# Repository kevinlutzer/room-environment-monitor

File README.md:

# Overview 

The Room Environment Monitor (REM) project was something that I started back in 2017. I wanted a small IoT device that could tell me if there was a concerning amount of volatile organic compounds (VOCs) and CO2 in my workshop. I built the first version based on a Raspberry Pi Zero, CCS811 air quality monitor, and a BME280 humidity and temperature sensor.

I went through multiple iterations of the project with the overall objective to reduce cost while increasing the precision of the measurements being made. At that time, the CCS811 sensor cost about 40 dollars alone, which brought the V1 bill of materials (BOM) cost to about 70 CAD. Fast forward to 2023, Ikea released their [Vindriktning](https://www.ikea.com/ca/en/p/vindriktning-air-quality-sensor-60515911/) air quality monitor which uses a [PM1006K](https://en.gassensor.com.cn/Product_files/Specifications/LED%20Particle%20Sensor%20PM1006K%20Specification.pdf) sensor to measure 2.5um matter in the air. I designed my latest version of the Room Environment Monitor to replace the controller inside and make use of the device's case.

# Data Collection

The REM collects data from the following sensors:
1. [BME280](https://www.bosch-sensortec.com/products/environmental-sensors/humidity-sensors-bme280/) - Temperature, Humidity, Pressure
1. [SGP40-2.5k](https://sensirion.com/products/catalog/SGP40) - VOCs, C02  
1. [PM1006K](https://en.gassensor.com.cn/ParticulateMatterSensor/info_itemid_105.html) - particulate matter in the air (2.5ug/m^3, 1.0ug/m^3, 10ug/m^3)

This data is then pushed to a MQTT broker via the MQTT networking protocal. The broker then broadcasts the data to any subscribers. I use [n8n](https://n8n.io/) which is a workflow automation tool to subscribe to the REM data stream. n8n ensures that each piece of data in this stream is inserted as a new row in to a Postgres database. Bellow is a sequence diagram that shows how the data flows and is collected. 

<!-- https://sequencediagram.org/
title Room Environment Monitor Data Collection 

REM->MQTT Broker:publish data over tcp/ip using MQTT
MQTT Broker->n8n:broad cast data over tcp/ip using MQTT 
n8n->Postgres: insert new row  -->

<!-- # Data Visualization -->

I use Grafana, a free an open source tool to visualize the collected data in my Postgres database. Here is a screenshot of the dashboard that I have created to visualize the data.

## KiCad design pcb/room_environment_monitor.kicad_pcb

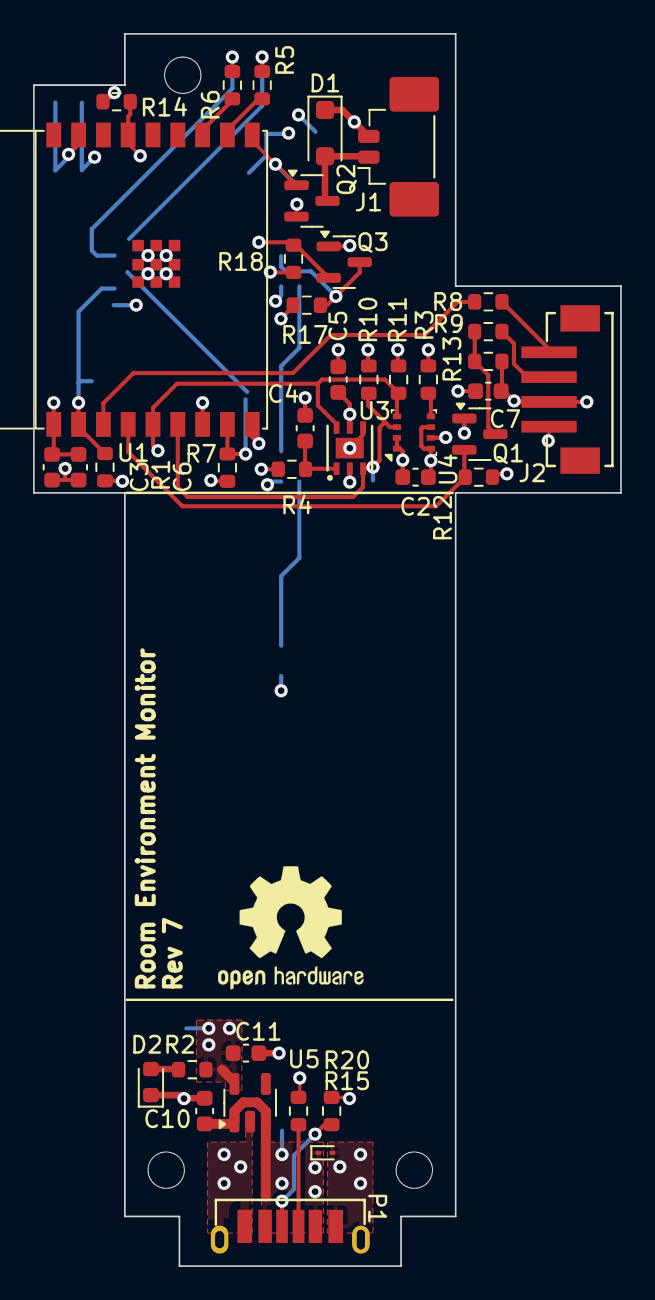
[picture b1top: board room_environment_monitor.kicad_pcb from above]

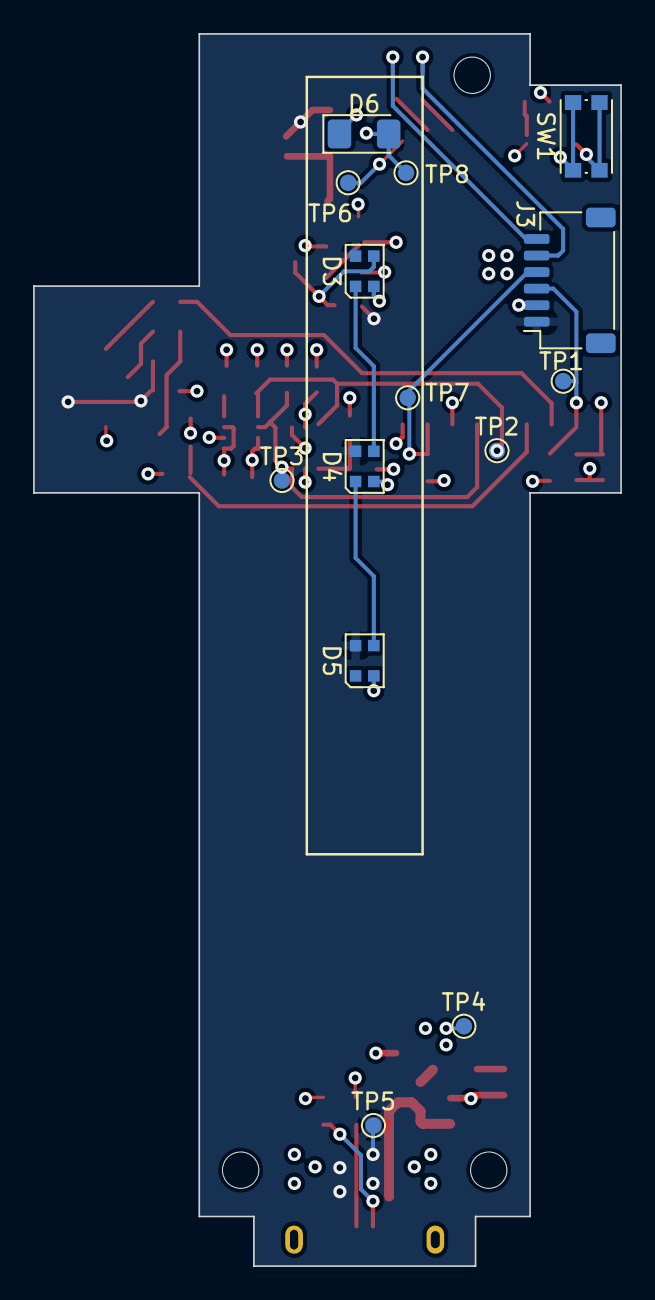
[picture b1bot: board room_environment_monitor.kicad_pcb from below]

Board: 4 copper layers, 35.5 x 74.5 mm, 56 parts (14 on the bottom side), 29 nets.

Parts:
C2, C3, C4, C5: 0u1; C_0603_1608Metric
C6, C7, C10, C11: 1u; C_0603_1608Metric
D1: CDBMS160; D_SOD-123F
D2: LED; LED_0603_1608Metric
D3, D4, D5: WS2812B-2020; LED_WS2812B-2020_PLCC4_2.0x2.0mm
D6: D_Photo; D_1206_3216Metric_Pad1.42x1.75mm_HandSolder
D7: ESD9X3; D_SOD-923
H1, H2, H3: MountingHole; MountingHole_2.2mm_M2_DIN965
J1: Conn_01x02_Pin; Molex_PicoBlade_53398-0271_1x02-1MP_P1.25mm_Vertical
J2: Conn_01x04_Pin; CONN_B4B-ZR-SM4-TF_JST
J3: Conn_01x06_Socket; JST_SH_SM06B-SRSS-TB_1x06-1MP_P1.00mm_Horizontal
P1: USB_C_Plug_USB2.0; CONN6_USB4130-GF-C_GCT
Q1, Q2, Q3: BSS138; SOT-23
R1, R3, R7, R12, R13, R17, R18: 10k; R_0603_1608Metric
R2: 220; R_0603_1608Metric
R4: 4.7; R_0603_1608Metric
R5, R6, R8, R9: 0; R_0603_1608Metric
R10, R11: 2k2; R_0603_1608Metric
R14: 10M; R_0603_1608Metric
R15, R20: 5.1k; R_0603_1608Metric
SW1: SW_SPST; SW_Push_1P1T_NO_CK_KMR2
TP1, TP2, TP3, TP4, TP5, TP6, TP7, TP8: TestPoint; TestPoint_Pad_D1.0mm
U1: ESP32-C3-WROOM-02
U3: SGP40; SGP30-2.5K_SEN-M
U4: BME280; Bosch_LGA-8_2.5x2.5mm_P0.65mm_ClockwisePinNumbering
U5: AP2112K-3.3; SOT-23-5

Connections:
+3V3: C2.1, C3.1, C5.1, C6.1, C11.1, D6.1 (K), Q1.1 (G), Q3.1 (G), R1.1, R2.1, R3.1, R4.1, R7.1, R10.2, R11.2, R12.1, R18.1, TP4.1, U1.1 (3V3), U3.5 (VDDH), U4.6 (VDDIO), U4.8 (VDD), U5.5 (VOUT)
+5V: C7.1, C10.1, D1.1 (K), D3.4 (VDD), D4.4 (VDD), D5.4 (VDD), D7.1 (K), J1.2, J2.3, J3.1, P1.A9 (VBUS), P1.B9 (VBUS), R13.1, R17.1, TP5.1, U5.1 (VIN), U5.3 (EN)
/NEOPIXEL_LVL: D3.3 (DIN), Q3.3 (D), R17.2
/Sensors/SGP30_VDD: C4.1, R4.2, U3.1 (VDD)
BOOT: J3.4, R7.2, TP7.1, U1.8 (GPIO9)
EN: J3.3, R1.2, TP1.1, U1.2 (EN/CHIP_PU)
FACT_REST: SW1.2 (B), U1.17 (GPIO1/ADC1_CH1/XTAL_32K_N)
FAN: Q2.1 (G), TP6.1, U1.10 (GPIO10)
GND: C2.2, C3.2, C4.2, C5.2, C6.2, C7.2, C10.2, C11.2, D2.1 (K), D3.2 (VSS), D4.2 (VSS), D5.2 (VSS), D7.2 (A), J2.4, J3.2, P1.A12 (GND), P1.B12 (GND), P1.S1 (SHIELD), Q2.2 (S), R14.1, R15.2, R20.2, SW1.1 (A), U1.9 (GND), U1.19 (GND), U3.2 (VSS), U3.4 (N/A), U3.7 (PAD), U4.1 (GND), U4.2 (CSB), U4.7 (GND), U5.2 (GND)
I2C_SCL: R11.1, TP2.1, U1.5 (GPIO6), U3.6 (SCL), U4.4 (SCK)
I2C_SDA: R10.1, TP3.1, U1.6 (GPIO7), U3.3 (SDA), U4.3 (SDI)
NEOPIXEL: Q3.2 (S), R18.2, U1.7 (GPIO8)
unnamed: D1.2 (A), J1.1, Q2.3 (D)
unnamed: D2.2 (A), R2.2
unnamed: D3.1 (DOUT), D4.3 (DIN)
unnamed: D4.1 (DOUT), D5.3 (DIN)
unnamed: J2.1, R8.1
unnamed: J2.2, R9.1
unnamed: J3.5, R6.2
unnamed: J3.6, R5.2
unnamed: P1.A5 (CC), R20.1
unnamed: P1.B5 (VCONN), R15.1
unnamed: R3.2, U4.5 (SDO)
PD: D6.2 (A), R14.2, TP8.1, U1.15 (GPIO3/ADC1_CH3)
UART1_RX: R8.2, U1.3 (GPIO4/ADC1_CH4)
UART1_TX: Q1.3 (D), R9.2, R13.2
UART1_TX_LVL: Q1.2 (S), R12.2, U1.4 (GPIO5/ADC2_CH0)
UART_RX: R6.1, U1.12 (GPIO21/U0TXD)
UART_TX: R5.1, U1.11 (GPIO20/U0RXD)

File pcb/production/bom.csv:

Designator,Footprint,Quantity,Value,LCSC Part #
"C1, C2, C3, C4, C5, C8",0603,6,0u1,
"C10, C11, C6, C7",0603,4,1u,
D1,D_SOD-123F,1,CDBMS160,
D2,0603,1,LED,
J1,Molex_PicoBlade_53398-0271_1x02-1MP_P1.25mm_Vertical,1,Conn_01x02_Pin,
J2,CONN_B4B-ZR-SM4-TF_JST,1,Conn_01x04_Pin,
"Q1, Q2",SOT-23,2,BSS138,
"R1, R12, R13, R16, R3, R7",0603,6,10k,
"R10, R11",0603,2,2k2,
"R15, R20",0603,2,5.1k,
R2,0603,1,220,
R4,0603,1,4.7,
"R5, R6, R8, R9",0603,4,0,
SW1,SW_Push_1P1T_NO_CK_KMR2,1,SW_SPST,
U1,DFN-8-1EP_3x2mm_P0.5mm_EP1.3x1.5mm,1,ATECC608A-MAHDA,
U2,ESP32-C3-MINI-1,1,ESP32-C3-MINI-1,
U3,SGP30-2.5K_SEN-M,1,SGP40,
U4,Bosch_LGA-8_2.5x2.5mm_P0.65mm_ClockwisePinNumbering,1,BME280,
U5,SOT-23-5,1,AP2112K-3.3,

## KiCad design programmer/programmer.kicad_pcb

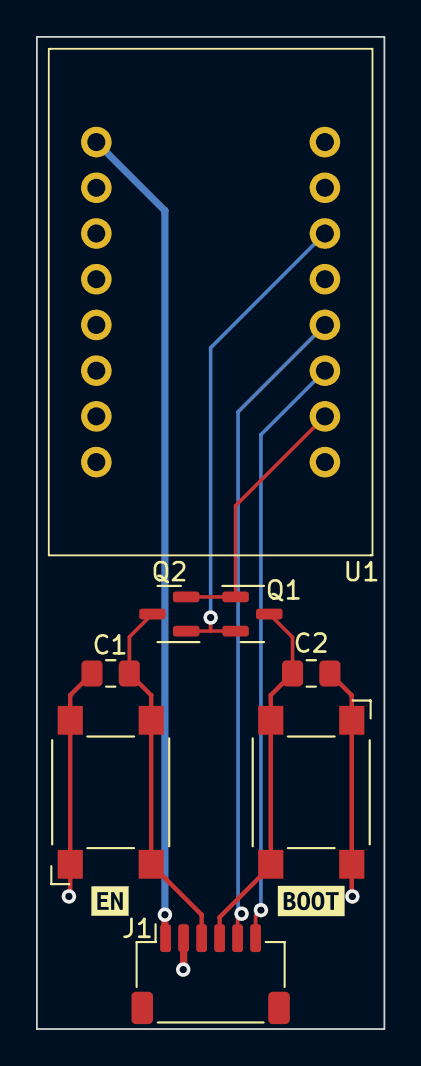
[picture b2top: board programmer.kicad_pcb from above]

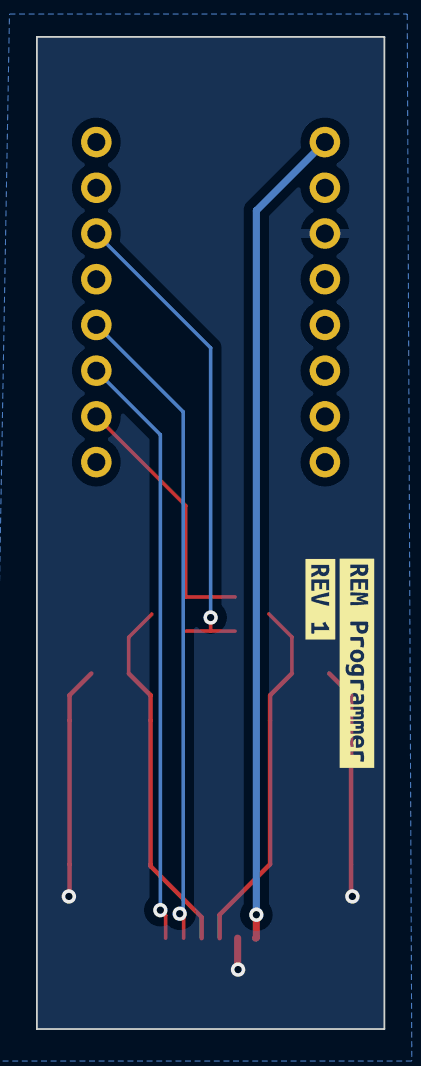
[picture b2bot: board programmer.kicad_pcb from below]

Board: 2 copper layers, 19.3 x 55.1 mm, 12 parts (2 on the bottom side), 8 nets.

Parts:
C1, C2: C; C_0805_2012Metric_Pad1.18x1.45mm_HandSolder
J1: Conn_01x06_Socket; JST_SH_SM06B-SRSS-TB_1x06-1MP_P1.00mm_Horizontal
Q1, Q2: BSS138; SOT-23
SW1, SW3: SW_Omron_B3FS; SW_SPST_Omron_B3FS-100xP
U1: Adafruit CP210XN Friend; Adafruit_CP210XN_Friend
kibuzzard-654D0F9E: G***; kibuzzard-654D0F9E
kibuzzard-654D0FC0: G***; kibuzzard-654D0FC0
kibuzzard-654D0FE8: G***; kibuzzard-654D0FE8
kibuzzard-654D1020: G***; kibuzzard-654D1020

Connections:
+5V: J1.1, U1.1 (VBUS)
BOOT: C2.1, J1.4, Q1.3 (D), SW3.2
DTR: Q1.2 (S), Q2.1 (G), U1.14 (DTR)
EN: C1.1, J1.3, Q2.3 (D), SW1.2
GND: C1.2, C2.2, J1.2, SW1.1, SW3.1, U1.3 (GND)
RTS: Q1.1 (G), Q2.2 (S), U1.10 (RTS)
UART_RX: J1.5, U1.12 (TXD)
UART_TX: J1.6, U1.11 (RXD)

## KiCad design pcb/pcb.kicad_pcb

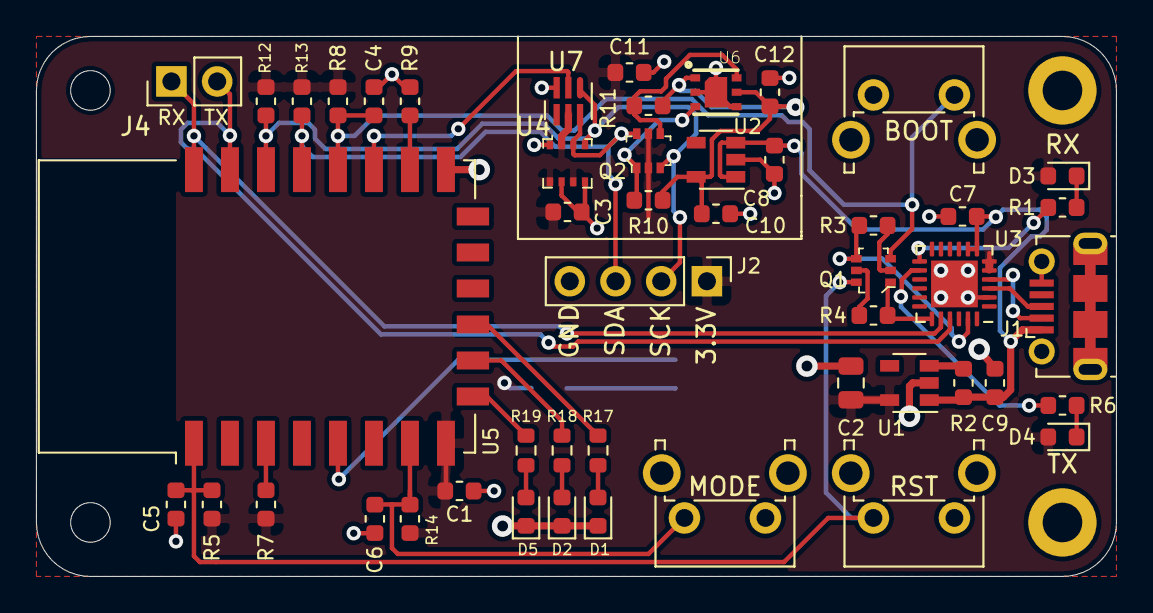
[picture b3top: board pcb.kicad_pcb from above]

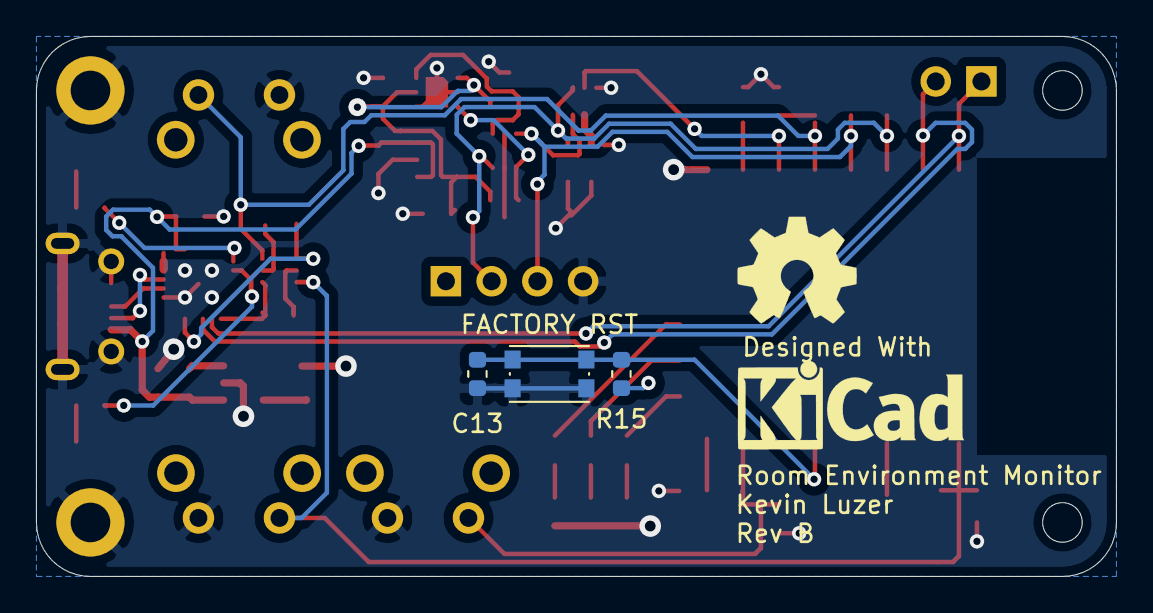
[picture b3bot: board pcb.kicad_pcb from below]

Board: 2 copper layers, 60.0 x 30.0 mm, 56 parts (3 on the bottom side), 34 nets.

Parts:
C1, C3, C4, C5, C6, C11, C12, C13: 100n; C_0603_1608Metric
C2: 47u; C_0805_2012Metric
C7, C8, C9, C10: 10u; C_0603_1608Metric
D1, D2, D3, D4, D5: LED; LED_0603_1608Metric
H1, H4: MountingHole_Pad; MountingHole_2.2mm_M2
H2, H3: MountingHole_Pad; MountingHole_2.2mm_M2_ISO14580_Pad
J1: USB_B_Mini; USB_Micro-B_Molex-105017-0001
J2: I2C_BUS; PinHeader_1x04_P2.54mm_Vertical
J4: UART_BUS; PinHeader_1x02_P2.54mm_Vertical
Q1, Q2: BSS138DW-7-F; SOT-363
R1, R6, R17, R18, R19: 470; R_0603_1608Metric
R2, R3, R4, R5, R7, R8, R9, R10, R11, R12, R13, R14, R15: 10k; R_0603_1608Metric
SW1, SW2, SW3: PTS645Vx83; SW_Tactile_SPST_Angled_PTS645Vx58-2LFS
SW4: KMR2; SW_Push_1P1T_NO_CK_KMR2
U1: AP2112K-3.3; SOT-23-5
U2: MIC5225-1.8YM5; SOT-23-5
U3: CP2104; QFN-24-1EP_4x4mm_P0.5mm_EP2.6x2.6mm
U4: BME280; Pressure_Sensor_LGA-8_2.5x2.5mm_BME280
U5: ESP-12F; ESP-12E
U6: SGP30
U7: TSL2591

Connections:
+1V8: C10.1, C12.1, R10.1, R11.1, U2.5, U6.1, U6.5
+3V3: C1.1, C2.1, C3.1, C11.1, D3.2, D4.2, J2.1, Q2.2, Q2.5, R5.1, R7.1, R8.1, R12.1, R13.1, R14.1, R15.1, U1.5, U3.5, U3.6, U4.2, U4.6, U4.8, U5.8, U7.5
+5V: C7.1, C8.1, C9.1, J1.1, R2.1, U1.1, U2.1, U2.3, U3.7, U3.8
GND: C1.2, C2.2, C3.2, C4.2, C5.2, C6.2, C7.2, C8.2, C9.2, C10.2, C11.2, C12.2, C13.2, D1.1, D2.1, D5.1, H2.1, H3.1, J1.5, J1.6, J2.4, R9.2, SW1.1, SW2.1, SW3.1, SW4.1, U1.2, U2.2, U3.2, U3.25, U4.1, U4.5, U4.7, U5.15, U6.2, U6.4, U6.7, U7.3
I2C_SCK: J2.2, Q2.3, R12.2, U4.4, U5.20, U7.1
I2C_SCK_1V8: Q2.4, R11.2, U6.6
I2C_SDA: J2.3, Q2.6, R13.2, U4.3, U5.19, U7.6
I2C_SDA_1V8: Q2.1, R10.2, U6.3
unnamed: D1.2, R17.1
unnamed: D2.2, R18.1
unnamed: D3.1, R1.1
unnamed: D4.1, R6.1
unnamed: D5.2, R19.1
unnamed: J1.2, U3.4
unnamed: J1.3, U3.3
unnamed: Q1.1, R4.2, U3.19
unnamed: Q1.2, R3.1
unnamed: Q1.4, R3.2, U3.23
unnamed: Q1.5, R4.1
unnamed: R1.2, U3.13
unnamed: R2.2, U1.3
unnamed: R6.2, U3.14
unnamed: R7.2, U5.3
unnamed: R9.1, U5.16
SIG1: R17.2, U5.11
SIG2: R18.2, U5.10
SIG3: R19.2, U5.9
UART_RX: J4.1, U3.20, U5.22
UART_TX: J4.2, U3.21, U5.21
nBOOT: C4.1, Q1.3, R8.2, SW2.2, U5.18
nFAC_RST: C13.1, R15.2, SW4.2, U5.5
nINT: U5.17, U7.2
nMODE: C6.1, R14.2, SW1.2, U5.7
nRST: C5.1, Q1.6, R5.2, SW3.2, U5.1

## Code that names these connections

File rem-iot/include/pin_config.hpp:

#ifndef _REM_PIN_CONFIG_HPP
#define _REM_PIN_CONFIG_HPP

#define PM1006K_RX_PIN 4
#define PM1006K_TX_PIN 5

#define FAN 10

#define I2C_SDA 7
#define I2C_SCL 6

#define NEOPIXEL_PIN 8
#define NUM_NEOPIXELS 3

#endif

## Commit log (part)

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2018-05-20 build iot functionality
2018-05-20 update service layer. Everything is working
2018-05-20 update main code for python to take in arguments to collect sensor data
2018-05-20 bring in dep
2018-05-20 fix import references
2018-05-20 remove uneeded commands
2018-05-20 file change
2018-05-20 WIP not sure why this isn't working --> Added io reader for std buffer
2018-05-21 WIP for concurrency
2018-05-21 Working version
2018-05-24 update service and sensor stuff
2018-05-24 add angular client
2018-05-26 make more progress on metric boxes
2018-05-26 add service and component
2018-05-26 refactor and make more progress flushing out the metric box
2018-05-29 add client files
2018-05-29 update logging
2018-05-29 get the server logs to make sense
2018-05-29 add python stub file
2018-05-29 update server logs
2018-09-12 update with cross platform compliation tool
2018-09-12 test signed
2018-09-13 add some base code I will need to in the entry point
2018-09-13 bring in gorobot
2018-09-13 refacor main.py to remove tsl stuff
2018-09-13 go fmt
2018-09-13 add binary file to gitignore list
2018-09-15 removed initaialize method until I can fix bugs in the gobot library
2018-09-15 use an api key
2018-09-15 update build deploy script so that it cleans up files and actually works
2018-09-15 add api key check in publish handler
2018-09-16 bring in base pubsub handler and refactor project structure
2018-09-16 get the pubsub handler working
2018-09-16 refactor for different projects
2018-09-17 refactor to use expressjs app
2018-09-19 create a new client every api request
2018-09-19 refactor the server setup
2018-09-22 Bring in fan control
2018-09-22 refactor
2018-09-23 add the fetch for room temperature in parallel
2018-09-23 refactor temperature fetching stuff
2018-09-23 Update some more stuff
2018-09-24 reafor more of the service
2018-09-25 Did some stuff and I don't remember what it was
2018-09-25 get a base function to work
2018-09-25 successfully move over experimental iot api stuff over to new structure
2018-09-25 rename file
2018-09-25 change the name of the file to be more orientated to the smart home action stuff
2018-09-26 refactor some logging
2018-09-28 Don't remember what I did. Committing work from a few days ago
2018-10-01 refactor results
2018-10-02 refactor to add humidity and pressure sensoring
2018-10-03 add the ability to shutdown server
2018-10-03 update room monitor code
2018-10-08 refactor the setup shell file
2018-10-08 properly exit
2018-10-10 refactor to remove cloud actions and fullfillment stuff
2018-10-11 get ride of actions stuff
2018-10-13 refactor more
2018-10-13 refactor to automate hostname and ip fetching
2018-10-13 refactor for new model name
2018-10-16 do something I forget
2018-10-20 refactor and add a config file
2018-10-20 get some of the send grid stuff working
2018-10-20 get the send grid stuff working
2018-10-20 refactor names to make more sense
2018-10-20 add all new files
2018-10-20 refactor name file
2018-10-20 build out the messaging stuff for status updates
2018-10-20 refacor more
2018-10-20 remove uneeded deps
2018-10-20 refactor and cleanup some more
2018-10-20 temporarily add room env control stuff for ifttt
2018-10-22 change the name of server to api
2018-10-22 Refactor some more'
2018-10-22 get the new architecture to work
2018-10-23 try and get the setup function to work
2018-10-23 add logger file
2018-10-23 refactor message for handling power status
2018-10-23 refactor name of config model
2018-10-23 bring in new entity for device status
2018-10-23 refactor and get the stuff to work
2018-10-23 added updated timestamp
2018-10-24 refactor time for status updates
2019-01-29 dep init and dep ensure
2019-01-30 main go to make it build
2019-01-30 refactor changes
2019-01-30 fix service
2019-01-30 update deps using vendor
2019-01-30 add mock files
2019-01-30 add base service test
2019-01-31 add some tests
2019-01-31 travis yml file
2019-01-31 update logger
2019-01-31 update vendor files
2019-01-31 add cron dep
2019-01-31 update travis ci for one build
2019-01-31 update service and tests
2019-01-31 add mockery fi;e
2019-02-01 write two tests and refactor the sensor service to not take in values
2019-02-02 remove uneeded logging and add some more tests
2019-02-02 handle errors from cron
2019-02-07 refactor how things are done
2019-02-07 add iot server
2019-02-07 update deps and update index ts
2019-02-07 update index
2019-02-07 change fiile names
2019-02-07 fix reference issues
2019-02-07 add status handler
2019-02-07 telemetry
2019-02-07 refacotr
2019-02-12 get the list api to work without response stuff
2019-02-18 refactor url for list telemetry
2019-12-25 switch to go mod
2020-01-19 stub out the iot service
2020-01-20 add some errors to exit on
2020-01-20 add stub service
2020-01-20 finally get the iot service stub to work
2020-01-20 rename all of the interfaces to Interface
2020-01-20 remove mock folder
2020-01-20 fix tests
2020-01-20 re add main
2020-01-20 refactor name
2020-01-25 add webhook cloud function
2020-01-26 update the depencies
2020-01-26 do some updating
2020-01-26 get the status handler working 100%
2020-01-28 try and do some stuff asyncronously
2020-01-28 move things around
2020-01-28 move everything around
2020-01-28 update the telemetry file
2020-01-28 refactor to get everything to work
2020-01-28 remove the pubsub handler that was scheduled
2020-01-28 add firestore indices
2020-01-28 clean up the telemetry
2020-01-31 try and add cors
2020-02-05 change name controllers to api
2020-02-05 remove firebase log file
2020-02-05 name change of api conversions
2020-02-05 refactor files and redploy pusubhandler
2020-02-05 remove command line interface
2020-02-05 remove the batch call
2020-02-05 get the telemetry event list working
2020-02-05 get the device list api to work
2020-02-05 remvoe debug logs
2020-02-06 fix the api interface to return hasMore and cursor
2020-02-06 remove uneeded imports
2020-02-06 add cors
2020-02-06 return the last active date
2020-02-06 last activity mutations
2020-02-13 all of the client files in to the client directory
2020-02-13 move the vscode config and internal files to client as wellg
2020-02-13 update the vscode config file
2020-02-13 add the documentation files
2020-02-27 refactor the go module name
2020-02-27 refactor so this works for every machine
2020-02-27 CRON
2020-02-27 set time limit to be 15 mins
2020-02-27 publish is using the right pattern
2020-02-27 remove the rest of the subscriptions
2020-02-27 refactor the cron values
2020-03-12 remove the error file and copy the constant to the main.go file
2020-03-28 get the case setup
2020-07-12 add pcb start with lipo battery charger
2020-07-14 update the pcb
2020-07-14 start the basis client v2
2020-07-14 setup the tsl init
2020-07-14 get the BME280 working
2020-07-20 finish the shcematic design
2020-07-21 get the update done on the pcb design, finish it
2020-07-29 remove the switch, add some more logic
2020-07-29 update the pcb stuff
2020-07-30 finish laying out most of the pcb parts
2020-07-31 finish the routing of the pcb all that is left is to clean up the silkscreen
2020-08-08 make last minute changes
2020-08-17 Update the gerbers for the rem v1 and reroute the UART lines
2020-08-18 fix tsl2691 component
2020-08-20 remove client
2020-08-20 rename client-v2 to client
2020-08-20 remove all the scripts
2020-08-20 add more comments to the pcb, cleanup board files
2020-09-01 update pcb rescue
2021-01-08 switch i2c lines around
2021-01-09 use the right tsl2591 footprint
2021-01-09 add autosave
2021-01-10 add zip file
2021-01-10 POWER
2021-01-10 update gerbers
2023-10-12 add images of v2 schematic and pcb
2023-10-13 remove backups
2023-10-13 bring in gitignore and v2 schematics
2023-10-13 move v2 gerbers
2023-10-15 get the schematic done, need to optomize for parts
2023-10-17 finish routing the PCB
2023-10-18 finish v4 and the images for doucmentation
2023-10-18 add bom
2023-10-19 cleanup undeeded pdf files and add gerbers
2023-10-30 add gerbers, ibom
2023-11-01 add the test and pm1006 base driver files
2023-11-05 add most of the controller code
2023-11-09 add the built programmer pcb, gerbers and bom
2023-11-09 rename v2 BOM
2023-11-09 switch the sda and scl lines on the SGP40
2023-11-09 Use a 4.7 ohm resistor for the RC Filter on the VDD for SGP40
2023-11-13 add the routing for hte PM1006K enable, and other fixes
2023-11-14 add debug and crendential classes
2023-11-15 update code wip
2023-11-16 Update documentation and images
2023-11-19 add new gerbers and bom, fix DRC and ERC for pcb
2023-11-19 update the documentation
2024-07-21 remove legacy server code, update ibom, etc
2024-08-10 add setup.sh, pcb and programmer files
2024-08-21 add the input/out via uart, tie everything to the terminal class, cleanup
2024-08-24 rename files for settings manager and add the settings interface
2024-08-24 move to platfomr io
2024-08-24 get things moved around
2024-08-31 fix eeprom issue
2024-09-02 terminal working
2024-09-02 implement reboot command
2024-09-02 format
2024-09-02 get print settings, debug toggling, and update settings working
2024-09-02 add wifi controller
2024-09-02 fix deivce id publishing for status
2024-09-03 move tasks into their own file
2024-09-04 refactor cli commands
2024-09-04 update the documentation for the rem code
2024-09-04 add a little bit to the readme for building and uploading the code. This needs more work. Also cleanup the vscode hidden files
2024-09-08 fix bug where I was using the ssid for the password when connecting to wifi on boot, cleanup printsize with a define
2024-09-08 cleanup comment in settings manager
2024-09-09 publish up time and rssi
2024-09-09 cleanup so I can build
2024-09-11 copy logic to tasks, cleanup sensor adapter
2024-09-11 finish refactor
2024-09-11 build out most of hte ledcontroller WIP
2024-09-14 add light controller and use it in the tasks
2024-09-25 create a generic providers class, this doesn't seem to be ideal as it creates a lot of circular depedencies
2024-09-28 update the triggers for the light to turn on
2024-10-01 feedback
2024-10-02 lint
2024-10-15 fix issue with string null terminations add setup script
2024-11-07 swap where the settings cli commands get swappedY
2024-11-16 fix the randomness of the uuid generation
2024-11-16 fix the randomness of the uuid generation (#9)
2024-11-18 Setup TZ w/ NTP | Turn off Neo Pixels at Night (#10)
    * zetup the time zone with ntp, turn off everything when at ngiht
    * Update rem-iot/src/main.cpp
    * Update rem-iot/lib/wifi-controller/wifi_controller.cpp
2024-12-25 Add new plugins for BOM and PNP file management
2025-01-13 added support for sgp40
2025-01-19 cleanup sensors
2025-01-19 move files
2025-04-09 lint and add justfile
2025-04-09 add the just file
2025-04-10 add pr workflow, dockerfile for cicd and justfile
2025-04-10 try something different
2025-04-10 platformio build
2025-04-10 redo the build command
2025-04-12 update workflow
2025-04-12 switch the trigger, get it to run
2025-04-12 build and lint
2025-04-12 use local libs
2025-04-12 build
2025-04-12 install clang format
2025-04-13 cleanup
2025-04-13 rename firmware files
2025-04-14 finish off firmware.ini
2025-04-14 update lint command ran
2025-04-14 use the firmware name
2025-04-14 firmware again
2025-04-14 up the sample rates to something more reasonable for the release
2025-04-14 add the roadmap file in place
2025-05-23 new line and erturn
2025-06-02 fix serialize documents
2025-06-02 formatting
2025-06-02 Fix Serialization Of Google Docs (#13)
    * fix serialize documents
    * bring back rssi
    * formatting
2025-06-03 fix memory leak
2025-06-03 bring back led
2025-06-04 Fix Memory Leak With Printing Data (#14)
    * fix memory leak
    * bring back led
    * cleanup
    * reconnect
    * lint
2025-08-03 do the reroute for the larger ESP32 module
2025-08-04 cleanup files
2025-08-07 add v6, remove all uneeded files
2025-08-31 Initial plan
2025-08-31 Initial exploration and analysis of codebase
2025-08-31 Add HTTP endpoint to return eth0 MAC address
